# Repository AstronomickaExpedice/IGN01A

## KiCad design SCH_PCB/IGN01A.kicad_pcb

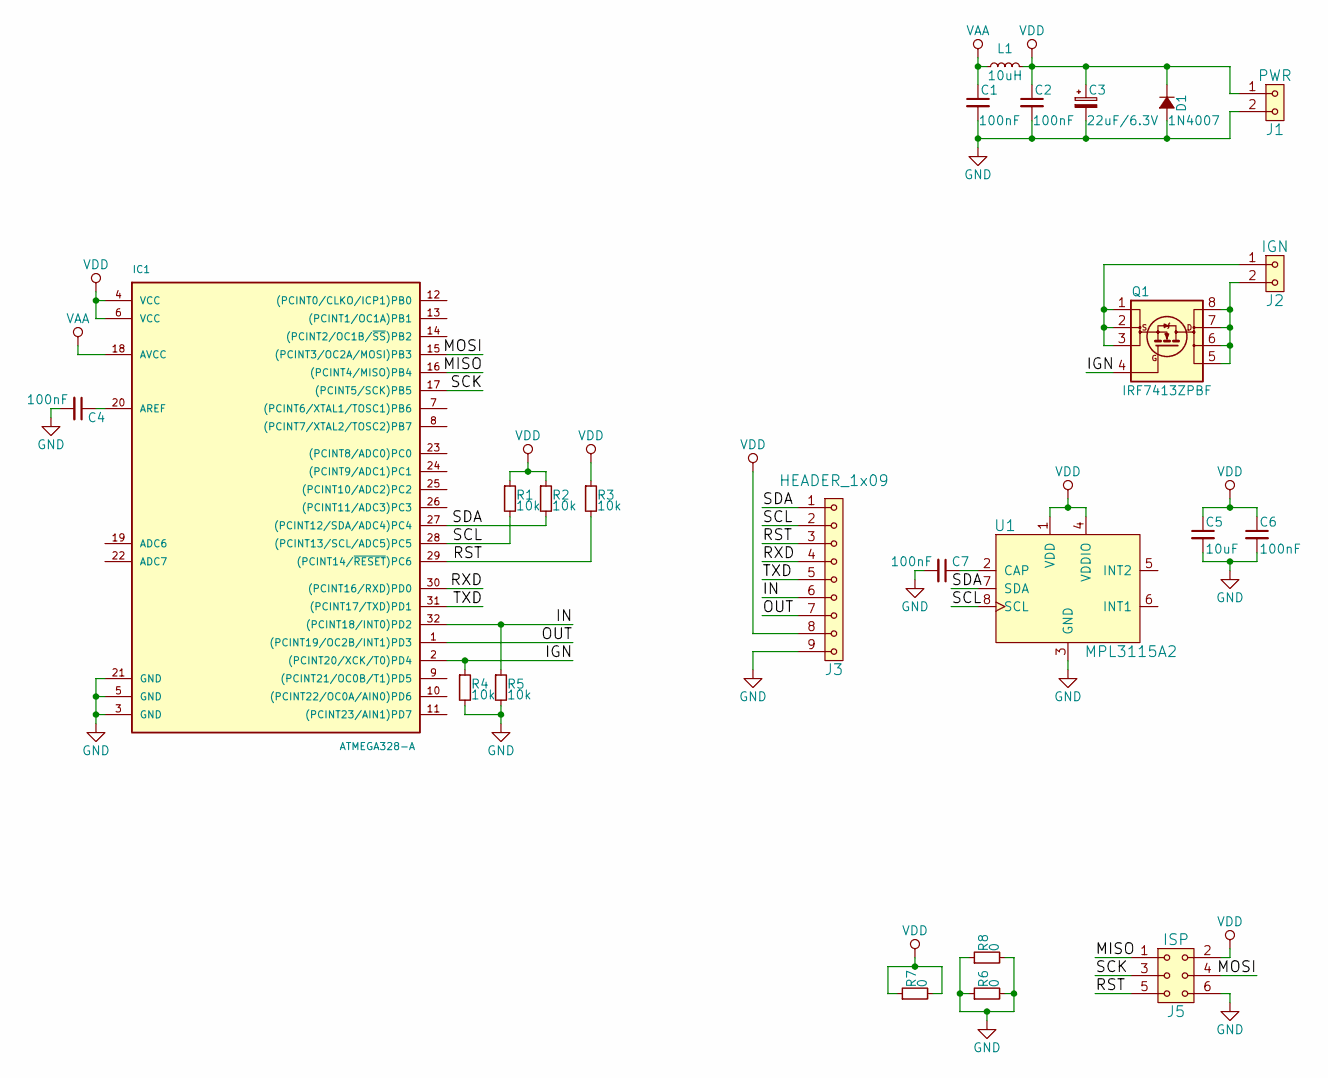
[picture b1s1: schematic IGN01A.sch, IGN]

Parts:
C1, C2, C4, C6, C7: 100nF; C_0805_HandSoldering
C3: 22uF/6.3V; C_0805_HandSoldering
C5: 10uF; C_0805_HandSoldering
D1: 1N4007; C_0805_HandSoldering
IC1: ATMEGA328-A; TQFP-32_7x7mm_Pitch0.8mm
J1: PWR; Angled_1x02
J2: IGN; Angled_1x02
J3: HEADER_1x09; Angled_1x09
J5: ISP; Straight_2x03
L1: 10uH; C_0805_HandSoldering
Q1: IRF7413ZPBF; SOIJ-8_5.3x5.3mm_Pitch1.27mm
R1, R2, R3, R4, R5: 10k; C_0805_HandSoldering
R6, R7, R8: 0; C_1206_HandSoldering
U1: MPL3115A2; LGA-MPL3115A

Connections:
/IGN: IC1.2 ((PCINT20/XCK/T0)PD4), Q1.4 (G), R4.1
/IN: IC1.32 ((PCINT18/INT0)PD2), J3.6, R5.1
/MISO: IC1.16 ((PCINT4/MISO)PB4), J5.1
/MOSI: IC1.15 ((PCINT3/OC2A/MOSI)PB3), J5.4
/OUT: IC1.1 ((PCINT19/OC2B/INT1)PD3), J3.7
/RST: IC1.29 ((PCINT14/~RESET~)PC6), J3.3, J5.5, R3.2
/RXD: IC1.30 ((PCINT16/RXD)PD0), J3.4
/SCK: IC1.17 ((PCINT5/SCK)PB5), J5.3
/SCL: IC1.28 ((PCINT13/SCL/ADC5)PC5), J3.2, R1.2, U1.8 (SCL)
/SDA: IC1.27 ((PCINT12/SDA/ADC4)PC4), J3.1, R2.2, U1.7 (SDA)
/TXD: IC1.31 ((PCINT17/TXD)PD1), J3.5
GND: C1.2, C2.2, C3.2, C4.2, C5.2, C6.2, C7.2, D1.2 (A), IC1.3 (GND), IC1.5 (GND), IC1.21 (GND), J1.2, J3.9, J5.6, R4.2, R5.2, R6.1, R6.2, R8.1, R8.2, U1.3 (GND)
unnamed: C4.1, IC1.20 (AREF)
unnamed: C7.1, U1.2 (CAP)
unnamed: J2.1, Q1.1 (S), Q1.2 (S), Q1.3 (S)
unnamed: J2.2, Q1.5 (D), Q1.6 (D), Q1.7 (D), Q1.8 (D)
VAA: C1.1, IC1.18 (AVCC), L1.1
VDD: C2.1, C3.1, C5.1, C6.1, D1.1 (K), IC1.4 (VCC), IC1.6 (VCC), J1.1, J3.8, J5.2, L1.2, R1.1, R2.1, R3.1, R7.1, R7.2, U1.1 (VDD), U1.4 (VDDIO)

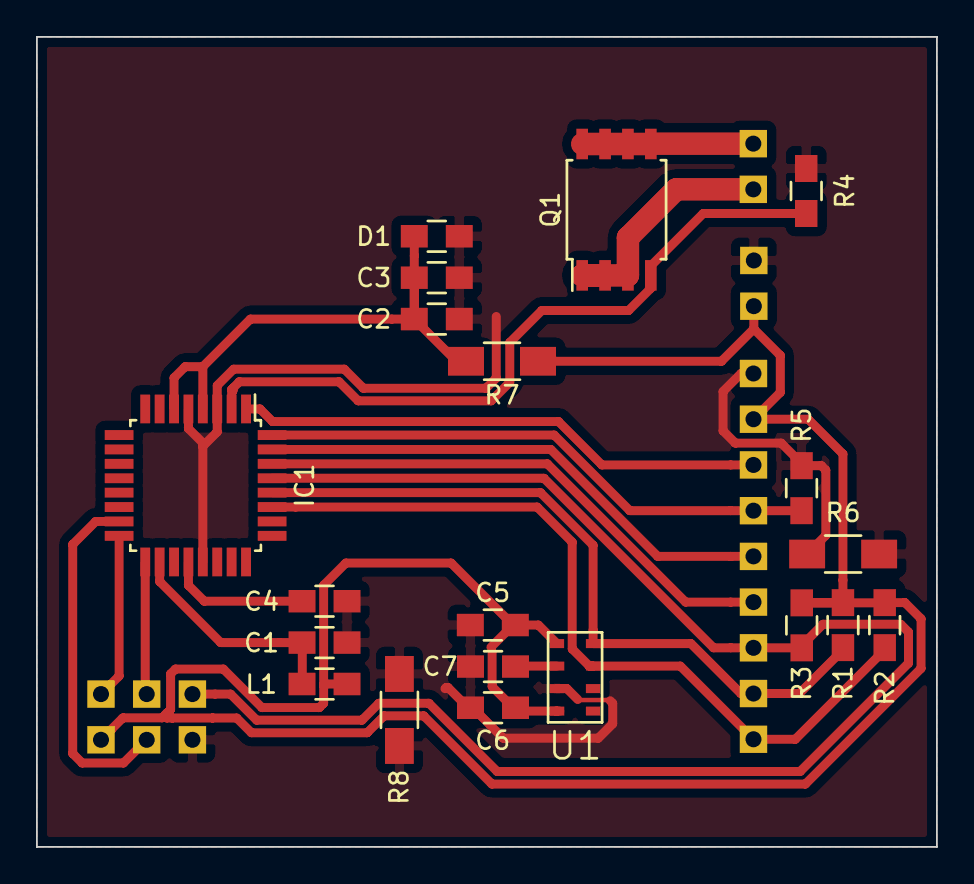
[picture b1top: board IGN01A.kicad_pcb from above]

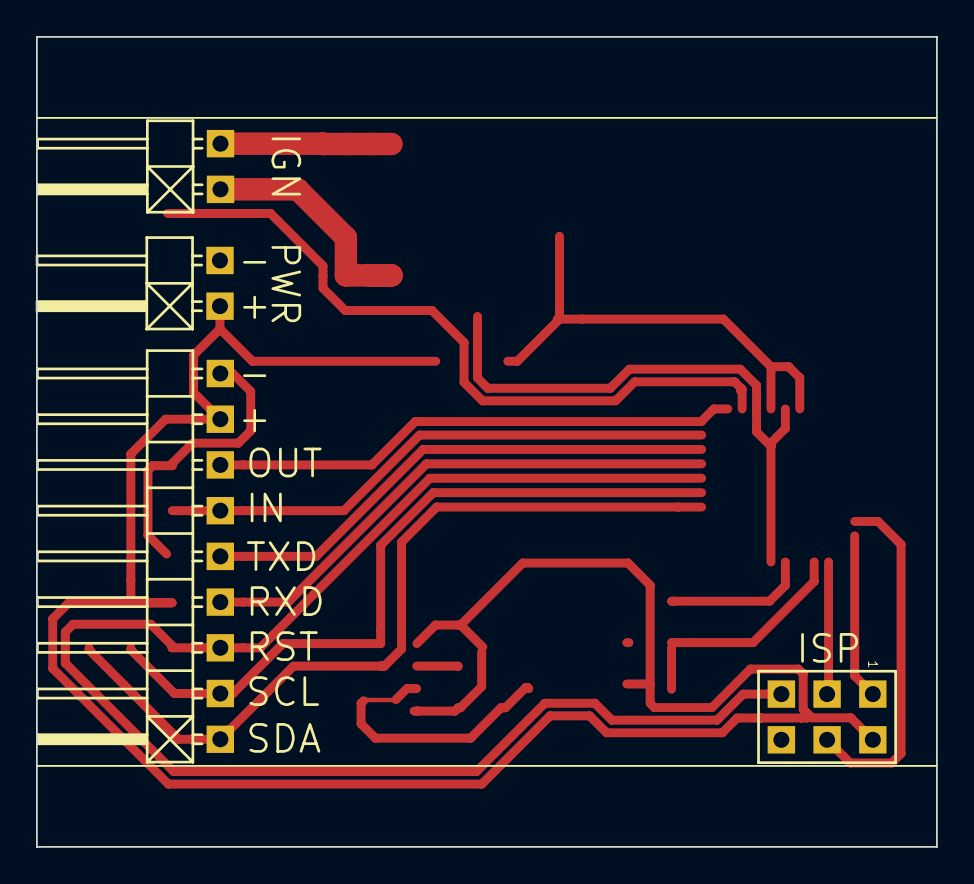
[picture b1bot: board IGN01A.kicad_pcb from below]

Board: 2 copper layers, 50.0 x 45.0 mm, 24 parts (4 on the bottom side), 18 nets.

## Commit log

2015-07-30 Removed unnesecary files
2015-07-31 Work on timers PCB started
2015-08-05 pcb added
2015-08-05 Better GND connection
2015-08-06 BOM generated
